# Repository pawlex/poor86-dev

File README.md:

# Poor86

A 386/486-class PC motherboard, in mini-ITX, built around a real x86 CPU
and an FPGA chipset — with every part of the machine that nobody loves
replaced by something modern.

It boots DOS. It has no hard disk, no battery, no legacy expansion
slots, no drive bays, and no shelf of discs. It fits in a case you can live with.

Decisions here are made on latency and phase coupling rather than raw
bandwidth: at 33 MHz with a four-word burst window, bandwidth is rarely
what binds. Slack is left in deliberately — spare capacity is usually
where the next idea lands.

Constraints are stated before solutions, and the reasoning behind each
decision is written down, wrong turns included. Source records what was
built; only a decision record explains why. That record is where the
project actually lives, and it is what would let someone else continue
the work rather than restart it.

---

## Why

### Love of the game

The interesting engineering is still here. A 486 local bus with burst
transfers, write-back cache control and coherency is a genuinely hard
problem, and building a chipset front end for it in programmable logic
is the kind of work that is worth doing for its own sake. The memory
subsystem and the bus interface caching are the heart of this project —
and they are deliberately scheduled **last**, because starting with the
best part is how the other ninety percent never gets finished.

### Giving back

The retro community has already solved most of the practical problems of
keeping these machines alive — floppy emulators, IDE replacements,
sound cards on modern microcontrollers, video scalers, USB adapters.
They exist as separate projects, separate purchases and separate wiring.

This assembles them into one board, and gives the work back: open
hardware, open RTL, and an entirely open toolchain (yosys, nextpnr,
Verilator — no vendor tools anywhere in the flow). Fixes found in
upstream projects go back upstream.

### The effort is already worth it, finished or not

This sat as an idea for years. Not for lack of interest — for lack of
time against its scope. It spans PCB design, an FPGA chipset, period bus
protocols, firmware, x86 emulation and controller software, and each of
those is somebody's full-time specialism. Any one of them is a weekend.
All of them together is a wall.

These sub-projects had been put off for years because they are hard —
but they are hard in a specific way that is worth naming, because it
changes what to do about them. **Most of them are wide, not deep.**

A deep problem needs insight you do not yet have. A wide one needs you
to be fluent in a domain you are not fluent in: the SeaBIOS source tree,
a Cirrus register map, an ECP5 memory primitive, the ATAPI packet
interface. Every step is tractable; the cost is the ramp-up, and it
resets every time you put the project down. That is precisely why wide
problems stall on evenings and weekends — the evening goes on reloading
context and never reaches the work.

Very little of the progress here came from cleverness. A months-old
question about the bus was answered by running one existing emulator
configuration. The peripheral models turned out to already exist in a
fork of the project. The video BIOS itself specified what the hardware
must implement, once somebody read it. None of that was hard. It was
*unread*.

Which leaves the genuinely deep part — the memory subsystem and the bus
interface caching — as the smallest fraction of the work, and the part
the author is actually equipped for. The wall was never the interesting
problem. It was the dozen uninteresting ones standing in front of it.

Working with an AI assistant (Claude) is what got past them. **And the
point worth making plainly is this: even if the board is never finished,
the effort has not been wasted.** Real problems have been solved, and they
stand on their own:

- **A working co-simulation harness.** An x86 interpreter running
  natively drives real RTL through a Wishbone bus-functional model, so
  chipset logic can be developed and regression-tested without a CPU in
  the simulation. It is reusable well beyond this project.
- **SeaBIOS completes POST against it**, on a non-PCI ISA machine with a
  deliberately minimal device set — a reproducible configuration, not a
  one-off.
- **A real bug found upstream**, in the tiny386 interpreter: its
  instruction-fetch cache retained a physical address for MMIO pages,
  reading out of bounds. Fixed, documented, and a candidate to send
  back.
- **A bounded specification for Cirrus-compatible video**, derived by
  reading what the video BIOS actually touches rather than guessing —
  including the finding that the blitter is not required at all.
- **Measured budgets rather than assumed ones** — bitstream size, block
  RAM limits, LUT and timing figures across candidate cores.

The larger shift is harder to point at but matters more. **A great deal
of this design has moved from "it could be done, with caveats" into an
active plan** — decisions made, alternatives eliminated for stated
reasons, and the reasoning written down where it can be checked. The
caveats that remain are now specific and small enough to attack.

Every decision here is the author's. The assistance is in reach and
throughput, and in not losing the reasoning between sessions — which,
for a project this wide worked on in evenings, turns out to be the
binding constraint.

**So this is also a case study**, kept in the open so it can be judged
rather than claimed. What has characterised it: check for the existing
thing before building a new one; measure instead of arguing; and keep
the corrections on the record — several conclusions in
[docs/PLAN_OF_RECORD.md](docs/PLAN_OF_RECORD.md) reversed once evidence arrived,
and the superseded reasoning still sits beside what replaced it.

There is a lot of noise about what this technology is for. This is one
answer: **real engineering problems, not cat videos.**

### Not just nostalgia

Nostalgia would mean reproducing a 1993 machine faithfully, defects
included, and accepting that it is expensive, fragile and annoying to
own. That is a museum piece.

The aim is different: **the era should be accessible to people who were
priced out of it, and pleasant enough to actually use.** Period hardware
has become scarce and costly; a working machine is now several hundred
pounds of separate purchases plus ongoing maintenance. This should cost
a fraction of that and ask nothing of its owner beyond plugging it in.

That said — the specific machines are not arbitrary. **A 386SX was the
author's first computer, and a 486SLC2 the first upgrade, paid for with
paper-round money.** Those configurations are a requirement, not a
technical trade-off. Everything modern in this design exists so that
*those* machines can be delivered without the burden that otherwise
makes them unusable.

---

## The organising principle

> **Authenticity is required at the guest-visible register interface.
> Everything behind it should be modern.**

A real x86 is soldered to this board. It, and the DOS software above it,
can only see registers and bus cycles — so that is the only place
period-correctness buys anything. Behind that boundary, reproducing 1993
is cost without benefit, and frequently worse: analogue output stages,
battery-backed NVRAM and spinning media are things to be rid of, not
honoured.

| | authentic front end | modern back end |
|---|---|---|
| storage | IDE / ATAPI registers | controller-served images |
| network | NE2000 registers | WiFi |
| keyboard, mouse | 8042 and PS/2 | USB HID |
| video | Cirrus-compatible registers | HDMI, or real CL-GD5428 for a CRT |
| RTC and CMOS | 128 legacy registers | NTP, no battery |
| sound | SB16 / AdLib registers | software synthesis, modern DAC |

Two corollaries that have saved a great deal of work:

- **Do not own what you can inherit.** SeaBIOS and SeaVGABIOS already
  support this machine. Shape the hardware so their existing code paths
  apply, rather than writing or patching firmware.
- **Do not reinvent what already exists.** Check first. Most of what
  this project needs has been found rather than written.

---

## Goals

- **Boots DOS**, on real x86 silicon, out of the box, with nothing
  attached.
- **mini-ITX (170 x 170 mm)**, in a case that can live on a desk.
- **Low bill of materials.** Every function moved into the FPGA or the
  board controller is a part that does not have to be bought, fitted or
  sourced.
- **Open end to end** — hardware, RTL, and toolchain.
- **No maintenance burden.** No battery to replace, no drive to fail, no
  media to store.
- **Usable by someone who is not the author**, which is a higher bar
  than working.

### Non-goals

- Museum-grade period accuracy behind the register interface.
- **Legacy expansion slots.** They do not fit the form factor, and
  building around scarce period cards is a dead end. Specific legacy
  silicon is supported directly, on a mezzanine; new work arrives on a
  modern header.
- Windows. DOS is the target; anything further is a bonus.
- Being the fastest anything. A period machine that works beats a fast
  one that does not exist.

---

## What is on the board

- **A soldered x86.** A 386/486 SL/SLC-class part, or an **Am5x86-133**
  — abundant as NOS, 486DX4-class, and the part that makes the machine
  more than a curiosity. **3.3 V is a requirement**, because it lets the
  entire CPU bus connect to the FPGA without level shifters — plausibly
  the largest single saving in the design.
- **An ECP5 FPGA** carrying the chipset and the peripherals, so a
  discrete 8259, 8254, 8042 and NE2000 are LUTs rather than packages.
- **An ESP32** as board controller: NTP for the clock, WiFi for the
  network, and the back end for storage.
- **A RISC-V soft core** inside the FPGA, which serves fallback
  configuration when the controller is unavailable, and which can run an
  x86 interpreter so that a board works with no period CPU fitted at all.
- **Video**, either from the FPGA over HDMI, or a real **CL-GD5428** on
  the local bus for driving a CRT.

*General placement only — orientation is not fixed. What is fixed is
which block connects to which FPGA edge, because that is derivable from
the datasheets now rather than discovered during layout. Pin counts are
counted from `Data/pinmap_*.csv`, not estimated. See
[PLACEMENT.md](docs/PLACEMENT.md).*

---

## Sub-projects

| repo | what it is | why it exists |
|---|---|---|
| [vexrv-cpu-oss](https://github.com/pawlex/vexrv-cpu-oss) | the RISC-V soft core, the x86 interpreter payload, and the Verilator co-simulation | the chipset is developed and debugged against it, so most of the machine can be made to work before a board exists |
| [ao486-cpu-oss](https://github.com/pawlex/ao486-cpu-oss) | the ao486 486-class x86 soft core packaged for the open toolchain — Verilator regression suite, plus synthesis and place-and-route with no vendor tools. Places and routes on an ECP5-85F at 32.87 MHz | **so the machine outlives the supply of period CPUs.** NOS Am5x86 is finite and not being made again; when it runs out, the board has to remain buildable, and a 486-class core inside the FPGA is how |
| [tiny386](https://github.com/pawlex/tiny386) | fork of the x86 interpreter, ported to bare-metal RV32 | gives the soft core an x86 to run, so a board with no period CPU fitted at all still boots |
| [ecp5-oss-skeleton](https://github.com/pawlex/ecp5-oss-skeleton) | ECP5 project template and the block-RAM findings behind it | keeps the entire flow on open tooling, with no vendor toolchain anywhere in it |

Firmware comes from [SeaBIOS](https://www.seabios.org/) and SeaVGABIOS,
unmodified where possible.

---

## Status

Early. The schematics and library work are in `PCB/`; reference material
is in `Data/`.

On the simulation side, SeaBIOS already completes POST against the
chipset model in Verilator, with real RTL in the transaction path.

**The memory subsystem and the bus interface caching are deliberately
unspecified.** They are the most interesting part of the work and they
are being left until the rest is done.

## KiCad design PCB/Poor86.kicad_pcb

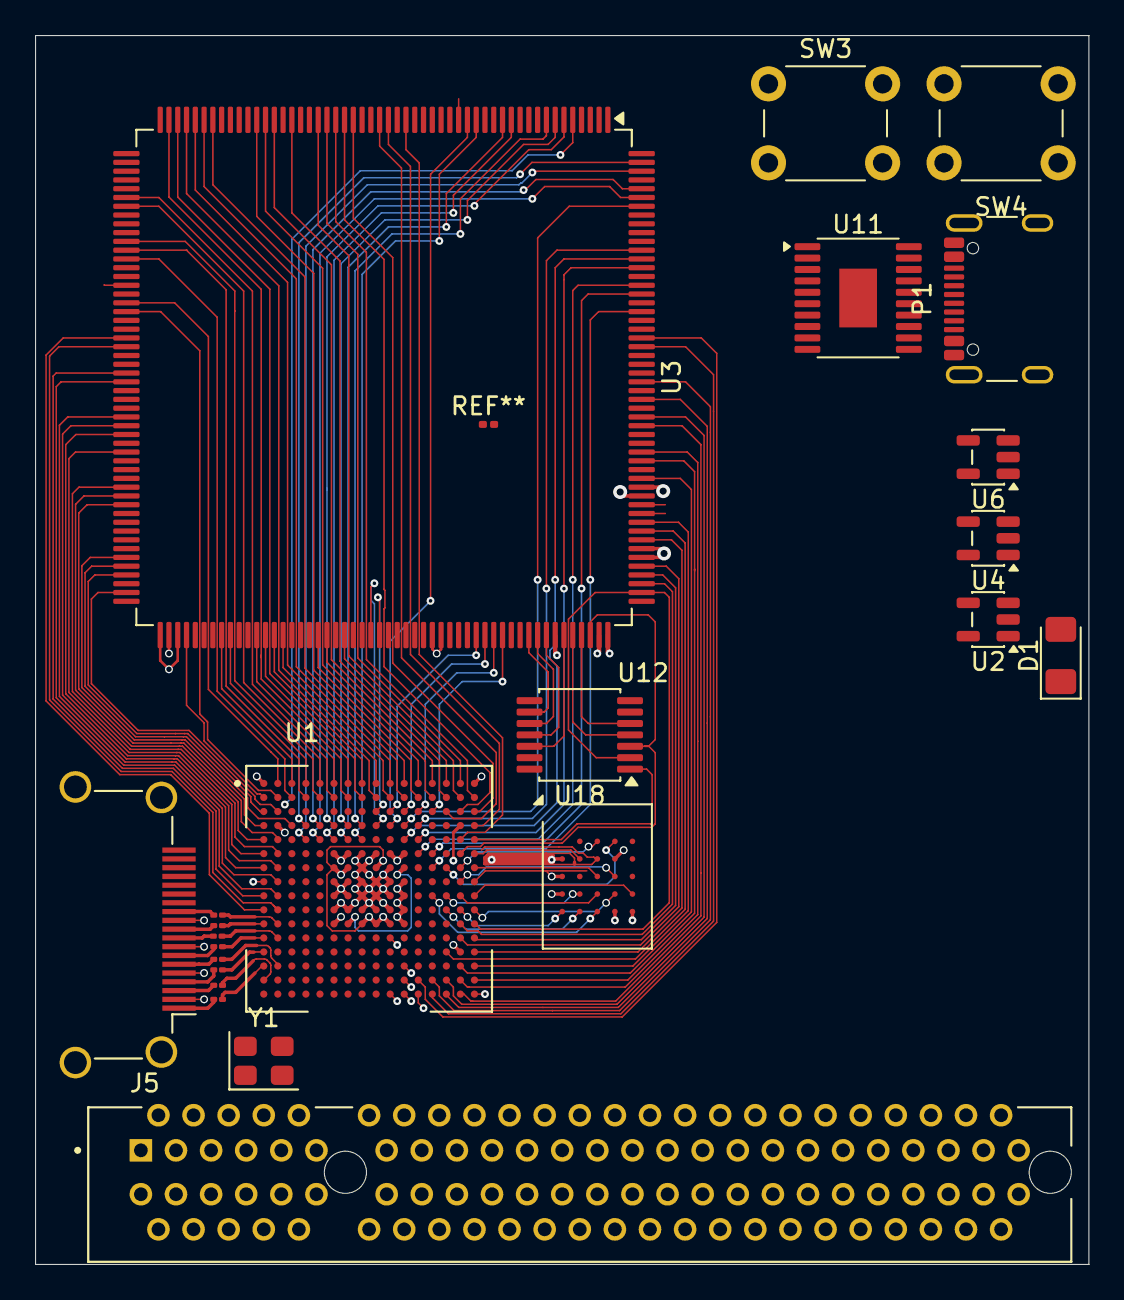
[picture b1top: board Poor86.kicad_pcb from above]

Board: 4 copper layers, 60.0 x 70.0 mm, 24 parts (1 on the bottom side), 143 nets.

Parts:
C35, C36, C45, C46, C47, C48, C49, C50: 2.2nF; C_01005_0402Metric
D1: 1N4001; D_1206_3216Metric_Pad1.42x1.75mm_HandSolder
J5: 10018783-10202TLF; AMPHENOL_10018783-10202TLF
J6: HDMI_A; HDMI_A_Amphenol_10029449-x01xLF_Horizontal
P1: USB_C_Plug_USB2.0; USB_C_Receptacle_GCT_USB4105-xx-A_16P_TopMnt_Horizontal
SW3, SW4: SW_Push_Dual; SW_PUSH_6mm
U1: LFE5U-25F-6BG256C; BGA256C80P16X16_1400X1400X170
U2, U4, U6: TLV62569DBV; SOT-23-5
U3: AM5x86 PQFP208; LQFP-208_28x28mm_P0.5mm
U5: ESP-12F; ESP-12E
U11: CH552T; TSSOP-20-1EP_4.4x6.5mm_P0.65mm_EP2.15x3.35mm
U12: IS66WVH8M8BLL-100B1LI; BGA-24_6x8mm_Layout5x5_P1.0mm
U18: 4068; TSSOP-14_4.4x5mm_P0.65mm
Y1: CMOS-50MHz; Oscillator_SMD_Abracon_ASE-4Pin_3.2x2.5mm

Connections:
+1V1: U1.G6 (VCC), U1.G7 (VCC), U1.G9 (VCC), U1.L8 (VCC), U1.L9 (VCC), U1.L10 (VCC)
+2V5: U1.G11 (VCCAUX), U1.L7 (VCCAUX)
+3V3: D1.2 (A), U1.F6 (VCCIO0), U1.F7 (VCCIO0), U1.F10 (VCCIO1), U1.F11 (VCCIO1), U1.H6 (VCCIO7), U1.H7 (VCCIO7), U1.H11 (VCCIO2), U1.J6 (VCCIO6), U1.J7 (VCCIO6), U1.J11 (VCCIO2), U1.K11 (VCCIO3), U1.L6 (VCCIO8), U1.L11 (VCCIO3), U3.2 (VCC), U3.9 (VCC), U3.14 (VCC), U3.19 (VCC), U3.20 (VCC), U3.22 (VCC), U3.23 (VCC), U3.25 (VCC), U3.29 (VCC), U3.35 (VCC), U3.38 (VCC), U3.42 (VCC), U3.44 (VCC), U3.45 (VCC), U3.54 (VCC), U3.56 (VCC), U3.60 (VCC), U3.62 (VCC), U3.69 (VCC), U3.77 (VCC), U3.80 (VCC), U3.82 (VCC), U3.86 (VCC), U3.89 (VCC), U3.95 (VCC), U3.98 (VCC), U3.102 (VCC), U3.106 (VCC), U3.111 (VCC), U3.114 (VCC), U3.121 (VCC), U3.128 (VCC), U3.131 (VCC), U3.133 (VCC), U3.134 (VCC), U3.136 (VCC), U3.137 (VCC), U3.139 (VCC), U3.150 (VCC), U3.155 (VCC), U3.162 (VCC), U3.163 (VCC), U3.169 (VCC), U3.172 (VCC), U3.176 (VCC), U3.179 (VCC), U3.183 (VCC), U3.185 (VCC), U3.188 (VCC), U3.191 (VCC), U3.198 (VCC), U3.200 (VCC), U3.205 (VCC), U12.B4 (VCC), U12.D1 (VCCQ), U12.E4 (VCCQ__1), U18.14 (Vdd), Y1.1 (EN), Y1.4 (Vdd)
+5V: U2.1 (EN), U2.4 (VIN), U4.1 (EN), U4.4 (VIN), U6.1 (EN), U6.4 (VIN)
/FPGA/DQ0: U1.J15 (PR23B), U12.D3 (DQ0)
/FPGA/DQ1: U1.J14 (PR20C), U12.D2 (DQ1)
/FPGA/DQ2: U1.H15 (PR20B), U12.C4 (DQ2)
/FPGA/DQ3: U1.K16 (PR23C), U12.D4 (DQ3)
/FPGA/DQ4: U1.J16 (PR23A), U12.D5 (DQ4)
/FPGA/DQ5: U1.J13 (PR17C), U12.E3 (DQ5)
/FPGA/DQ6: U1.K14 (PR20D), U12.E2 (DQ6)
/FPGA/DQ7: U1.K15 (PR23D), U12.E1 (DQ7)
/FPGA/OB_CLKt: U1.F16 (PR14A), U12.B2 (CK)
/FPGA/OB_RWDS: U1.G16 (PR20A), U12.C3 (RWDS)
/FPGA/~CS: U1.G15 (PR14B), U1.N8 (PB15A), U12.A3 (~CS)
/FPGA/~RESET: U1.G14 (PR14C), U12.A4 (~RESET)
/eternal_perif/CK+: C49.1, U1.L1 (PL26A)
/eternal_perif/CK-: C50.1, U1.L2 (PL26B)
/eternal_perif/D0+: C47.1, U1.M1 (PL26C)
/eternal_perif/D0-: C48.1, U1.M2 (PL26D)
/eternal_perif/D1+: C45.1, U1.N1 (PL32A)
/eternal_perif/D1-: C46.1, U1.P2 (PL32B)
/eternal_perif/D2+: C35.1, U1.P1 (PL35A)
/eternal_perif/D2-: C36.1, U1.R1 (PL35B)
A2: U1.D11 (PT51A), U3.202 (A2)
A3: U1.D12 (PT58A), U3.197 (A3)
A4: U1.E11 (PT51B), U3.196 (A4)
A5: U1.E12 (PT58B), U3.195 (A5)
A6: U1.F12 (PR8D), U3.193 (A6)
A7: U1.F13 (PR8C), U3.192 (A7)
A8: U1.G13 (PR11B), U3.190 (A8)
A9: U1.R12 (PR44A), U3.187 (A9)
A10: U1.T13 (PR44B), U3.186 (A10)
A11: U1.R13 (PR41C), U3.182 (A11)
A12: U1.T14 (PR41D), U3.180 (A12)
A13: U1.R14 (PR41B), U3.178 (A13)
A14: U1.T15 (PR38D), U3.177 (A14)
A15: U1.R15 (PR38C), U3.174 (A15)
A16: U1.R16 (PR35B), U3.173 (A16)
A17: U1.P15 (PR32B), U3.171 (A17)
A18: U1.P16 (PR35A), U3.166 (A18)
A19: U1.N14 (PR35D), U3.165 (A19)
A20: U1.N16 (PR32A), U3.164 (A20)
A21: U1.M15 (PR26D), U3.161 (A21)
A22: U1.M16 (PR26C), U3.160 (A22)
A23: U1.L15 (PR26B), U3.159 (A23)
A24: U1.L16 (PR26A), U3.158 (A24), U18.2 (A)
A25: U1.F15 (PR11C), U3.154 (A25), U18.3 (B)
A26: U3.153 (A26), U18.5 (D)
A27: U3.152 (A27), U18.4 (C)
A28: U3.151 (A28), U18.12 (H)
A29: U3.149 (A29), U18.11 (G)
A30: U3.148 (A30), U18.10 (F)
A31: U3.147 (A31), U18.9 (E)
AHOLD: U1.D10 (PT47A), U3.17 (AHOLD)
BREQ: U1.C16 (PR5A), U3.30 (BREQ)
CLK: U1.E15 (PR8B), U3.24 (CLK)
D0: U1.C13 (PT60B), U3.144 (D0)
D1: U1.C12 (PT56B), U3.143 (D1)
D2: U1.C11 (PT49B), U3.142 (D2)
D3: U1.C10 (PT44B), U3.141 (D3)
D5: U1.C9 (PT38B), U3.130 (D5)
D6: U1.D9 (PT40A), U3.129 (D6)
D7: U1.A14 (PT65B), U3.126 (D7)
D8: U1.B13 (PT60A), U3.124 (D8)
D9: U1.B12 (PT56A), U3.123 (D9)
D10: U1.A9 (PT42A), U3.119 (D10)
D11: U1.A8 (PT29B), U3.118 (D11)
D12: U1.A7 (PT29A), U3.117 (D12)
D13: U1.A6 (PT18B), U3.116 (D13)
D14: U1.A4 (PT6B), U3.113 (D14)
D15: U1.A3 (PT6A), U3.112 (D15)
D16: U1.B1 (PL2A), U3.108 (D16)
D17: U1.C2 (PL5B), U3.103 (D17)
D18: U1.C1 (PL5A), U3.101 (D18)
D19: U1.D3 (PL2D), U3.100 (D19)
D20: U1.D1 (PL8A), U3.99 (D20)
D21: U1.E2 (PL8B), U3.93 (D21)
D22: U1.E1 (PL11D), U3.92 (D22)
D23: U1.F2 (PL11C), U3.91 (D23)
D24: U1.F1 (PL14A), U3.87 (D24)
D25: U1.G2 (PL14B), U3.85 (D25)
D26: U1.G1 (PL20A), U3.84 (D26)
D27: U1.H2 (PL20B), U3.83 (D27)
D28: U1.J2 (PL23B), U3.79 (D28)
D29: U1.J1 (PL23A), U3.78 (D29)
D30: U1.K2 (PL23D), U3.75 (D30)
D31: U1.K1 (PL23C), U3.74 (D31)
D~C: U1.A13 (PT65A), U3.39 (D~C)
GNDD: J6.2 (D2S), J6.5 (D1S), J6.8 (D0S), J6.11 (CKS), J6.17 (GND), J6.SH, U1.A1 (GND1), U1.A16 (GND1), U1.D2 (GND1), U1.D15 (GND1), U1.F8 (GND1), U1.F9 (GND1), U1.G8 (GND1), U1.G10 (GND1), U1.H1 (GND1), U1.H8 (GND1), U1.H9 (GND1), U1.H10 (GND1), U1.H16 (GND2), U1.J8 (GND2), U1.J9 (GND2), U1.J10 (GND2), U1.K6 (GND2), U1.K7 (GND2), U1.K8 (GND2), U1.K9 (GND2), U1.K10 (GND2), U1.N2 (GND2), U1.N15 (GND2), U1.T1 (GND2), U1.T5 (GND2), U1.T12 (GND2), U1.T16 (GND2), U2.2 (GND), U3.1 (GND), U3.10 (GND), U3.15 (GND), U3.21 (GND), U3.28 (GND), U3.36 (GND), U3.43 (GND), U3.52 (GND), U3.53 (GND), U3.55 (GND), U3.57 (GND), U3.61 (GND), U3.76 (GND), U3.81 (GND), U3.88 (GND), U3.94 (GND), U3.97 (GND), U3.104 (GND), U3.105 (GND), U3.107 (GND), U3.110 (GND), U3.115 (GND), U3.120 (GND), U3.122 (GND), U3.132 (GND), U3.135 (GND), U3.138 (GND), U3.146 (GND), U3.156 (GND), U3.157 (GND), U3.170 (GND), U3.175 (GND), U3.181 (GND), U3.184 (GND), U3.189 (GND), U3.199 (GND), U3.201 (GND), U3.208 (GND), U4.2 (GND), U6.2 (GND), U11.18 (GND), U12.B1 (~CK), U12.B3 (VSS), U12.C1 (VSSQ), U12.E5 (VSSQ__1), U18.7 (Vss), Y1.2 (GND)
HOLD: U1.E8 (PT33A), U3.16 (HOLD)
HOLDA: U1.D16 (PR8A), U3.26 (HOLDA)
INTR: U1.B8 (PT35B), U3.50 (INTR)
INV: U1.B2 (PL2B), U3.71 (INV)
LRC_GPLL0T_IN: U1.P11 (PR47C), Y1.3 (OUT)
M~IO: U1.B14 (PT67A), U3.37 (M~IO)
NMI: U1.B7 (PT27B), U3.51 (NMI)
unnamed: D1.1 (K), SW3.2, SW4.2, U11.20 (3V3)
unnamed: C49.2, J6.10 (CK+)
unnamed: C50.2, J6.12 (CK-)
unnamed: C47.2, J6.7 (D0+)
unnamed: C48.2, J6.9 (D0-)
unnamed: C45.2, J6.4 (D1+)
unnamed: C46.2, J6.6 (D1-)
unnamed: C35.2, J6.1 (D2+)
unnamed: C36.2, J6.3 (D2-)
unnamed: P1.A6 (D+), U11.14 (P36)
unnamed: P1.A7 (D-), U11.15 (P37)
unnamed: P1.A1 (GND), P1.A12 (GND), P1.B1 (GND), P1.B12 (GND)
unnamed: U1.M10 (TDO), U3.168 (TDI)
unnamed: SW3.1, U11.6 (RST)
unnamed: P1.A4 (VBUS), P1.A9 (VBUS), P1.B4 (VBUS), P1.B9 (VBUS), U11.19 (VBUS)
PCD: U1.A11 (PT53A), U3.41 (PCD)
PWT: U1.A12 (PT53B), U3.40 (PWT)
RESET: U1.B10 (PT44A), U3.48 (RESET)
SRESET: U1.B6 (PT22B), U3.58 (SRESET)
TCK: U1.T10 (TCK), U3.18 (TCK), U11.5 (P17)
TDI: U1.R11 (TDI), U11.3 (P15)
TDO: U3.68 (TDO), U11.4 (P16)
TMS: U1.T11 (TMS), U3.167 (TMS), U11.2 (P14)
UADDR: U1.E16 (PR11D), U18.1 (K)
WB~WT: U1.B4 (PT11B), U3.64 (WB~WT)
W~R: U1.C14 (PR2C), U3.27 (W~R)
~A20M: U1.A10 (PT42B), U3.47 (~A20M)
~ADS: U1.E5 (PT13A), U3.203 (~ADS)
~BE0: U1.C15 (PR5B), U3.31 (~BE0)
~BE1: U1.B16 (PR2A), U3.32 (~BE1)
~BE2: U1.A15 (PT67B), U3.33 (~BE2)
~BE3: U1.B15 (PR2B), U3.34 (~BE3)
~BLAST: U1.D5 (PT13B), U3.204 (~BLAST)
~BOFF: U1.D6 (PT20B), U3.6 (~BOFF)
~BS8: U1.D8 (PT33B), U3.8 (~BS8)
~BS16: U1.D7 (PT24B), U3.7 (~BS16)
~CACHE: U1.A2 (PT4A), U3.70 (~CACHE)
~EADS: U1.B11 (PT49A), U3.46 (~EADS)
~FLUSH: U1.B9 (PT38A), U3.49 (~FLUSH)
~HITM: U1.B5 (PT15B), U3.63 (~HITM)
~KEN: U1.E7 (PT24A), U3.13 (~KEN)
~LOCK: U1.D4 (PT9B), U3.207 (~LOCK)
~PLOCK: U1.E4 (PT9A), U3.206 (~PLOCK)
~RDY: U1.E6 (PT20A), U3.12 (~RDY)
~SMIACT: U1.A5 (PT18A), U3.59 (~SMIACT)
~SMI: U1.B3 (PT4B), U3.65 (~SMI)
